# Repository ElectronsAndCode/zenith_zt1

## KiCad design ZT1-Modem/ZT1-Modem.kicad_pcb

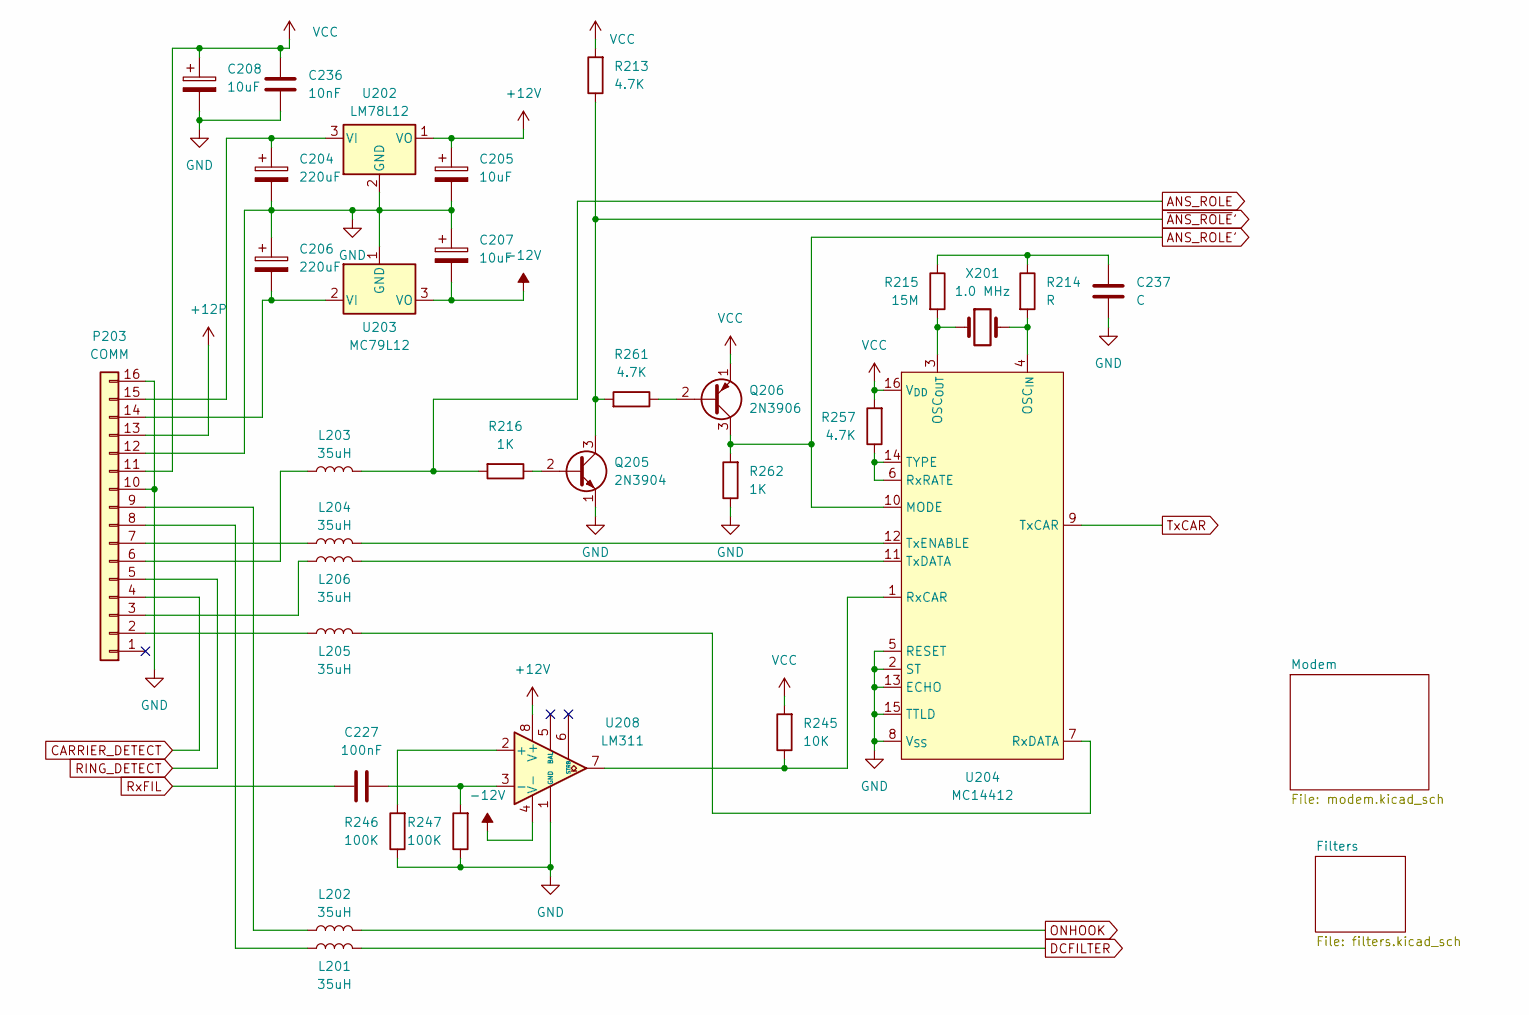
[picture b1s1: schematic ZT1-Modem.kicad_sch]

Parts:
C204, C206: 220uF; CP_Radial_Tantal_D9.0mm_P5.00mm
C205, C207, C208: 10uF; CP_Radial_Tantal_D5.0mm_P2.50mm
C227: 100nF; C_300mil
C236: 10nF; C_10mm
C237: C; C_10mm
L201, L202, L203, L204, L205, L206: 35uH; L_150mil
P203: COMM; PinHeader_1x16_P2.54mm_Vertical
Q205: 2N3904; TO-92_Inline_Wide
Q206: 2N3906; TO-92_Inline_Wide
R213, R257, R261: 4.7K; R
R214: R
R215: 15M; R
R216, R262: 1K; R
R245: 10K; R
R246, R247: 100K; R
U202: LM78L12; TO-92_Inline_Wide
U203: MC79L12; TO-92_Inline_Wide
U204: MC14412; DIP-16_W7.62mm
U208: LM311; DIP-8_W7.62mm
X201: 1.0 MHz; Crystal_HC33-U_Vertical

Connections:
+12P: P203.13; also elsewhere on the board
+12V: C205.1, U202.1 (VO), U208.8 (V+); also elsewhere on the board
-12V: C207.2, U203.3 (VO), U208.4 (V-); also elsewhere on the board
ANS_ROLE: L203.2, R216.2; also elsewhere on the board
ANS_ROLE': Q206.3 (C), R262.2, U204.10 (MODE); also elsewhere on the board
CARRIER_DETECT: P203.4; also elsewhere on the board
DCFILTER: L201.1; also elsewhere on the board
GND: C204.2, C205.2, C206.1, C207.1, C208.2, C236.1, C237.2, P203.10, P203.12, P203.16, Q205.1 (E), R246.1, R247.1, R262.1, U202.2 (GND), U203.1 (GND), U204.2 (ST), U204.5 (RESET), U204.8 (V_{SS}), U204.13 (ECHO), U204.15 (TTLD), U208.1 (GND); also elsewhere on the board
unnamed: C237.1, R214.1, R215.1
unnamed: L205.2, P203.2
unnamed: L206.1, P203.3
unnamed: L203.1, P203.6
unnamed: L204.1, P203.7
unnamed: L201.2, P203.8
unnamed: L202.2, P203.9
unnamed: C206.2, P203.14, U203.2 (VI)
unnamed: C204.1, P203.15, U202.3 (VI)
unnamed: Q205.2 (B), R216.1
unnamed: Q206.2 (B), R261.1
unnamed: R214.2, U204.4 (OSC_{IN}), X201.2
unnamed: R215.2, U204.3 (OSC_{OUT}), X201.1
unnamed: R245.1, U204.1 (RxCAR), U208.7
unnamed: L205.1, U204.7 (RxDATA)
unnamed: R257.1, U204.6 (RxRATE), U204.14 (TYPE)
unnamed: L206.2, U204.11 (TxDATA)
unnamed: L204.2, U204.12 (TxENABLE)
unnamed: R246.2, U208.2 (+)
unnamed: C227.2, R247.2, U208.3 (-)
ONHOOK: L202.1; also elsewhere on the board
RING_DETECT: P203.5; also elsewhere on the board
RxFIL: C227.1; also elsewhere on the board
TxCAR: U204.9 (TxCAR); also elsewhere on the board
VCC: C208.1, C236.2, P203.11, Q206.1 (E), R213.2, R245.2, R257.2, U204.16 (V_{DD}); also elsewhere on the board
~ANS_ROLE': Q205.3 (C), R213.1, R261.2; also elsewhere on the board

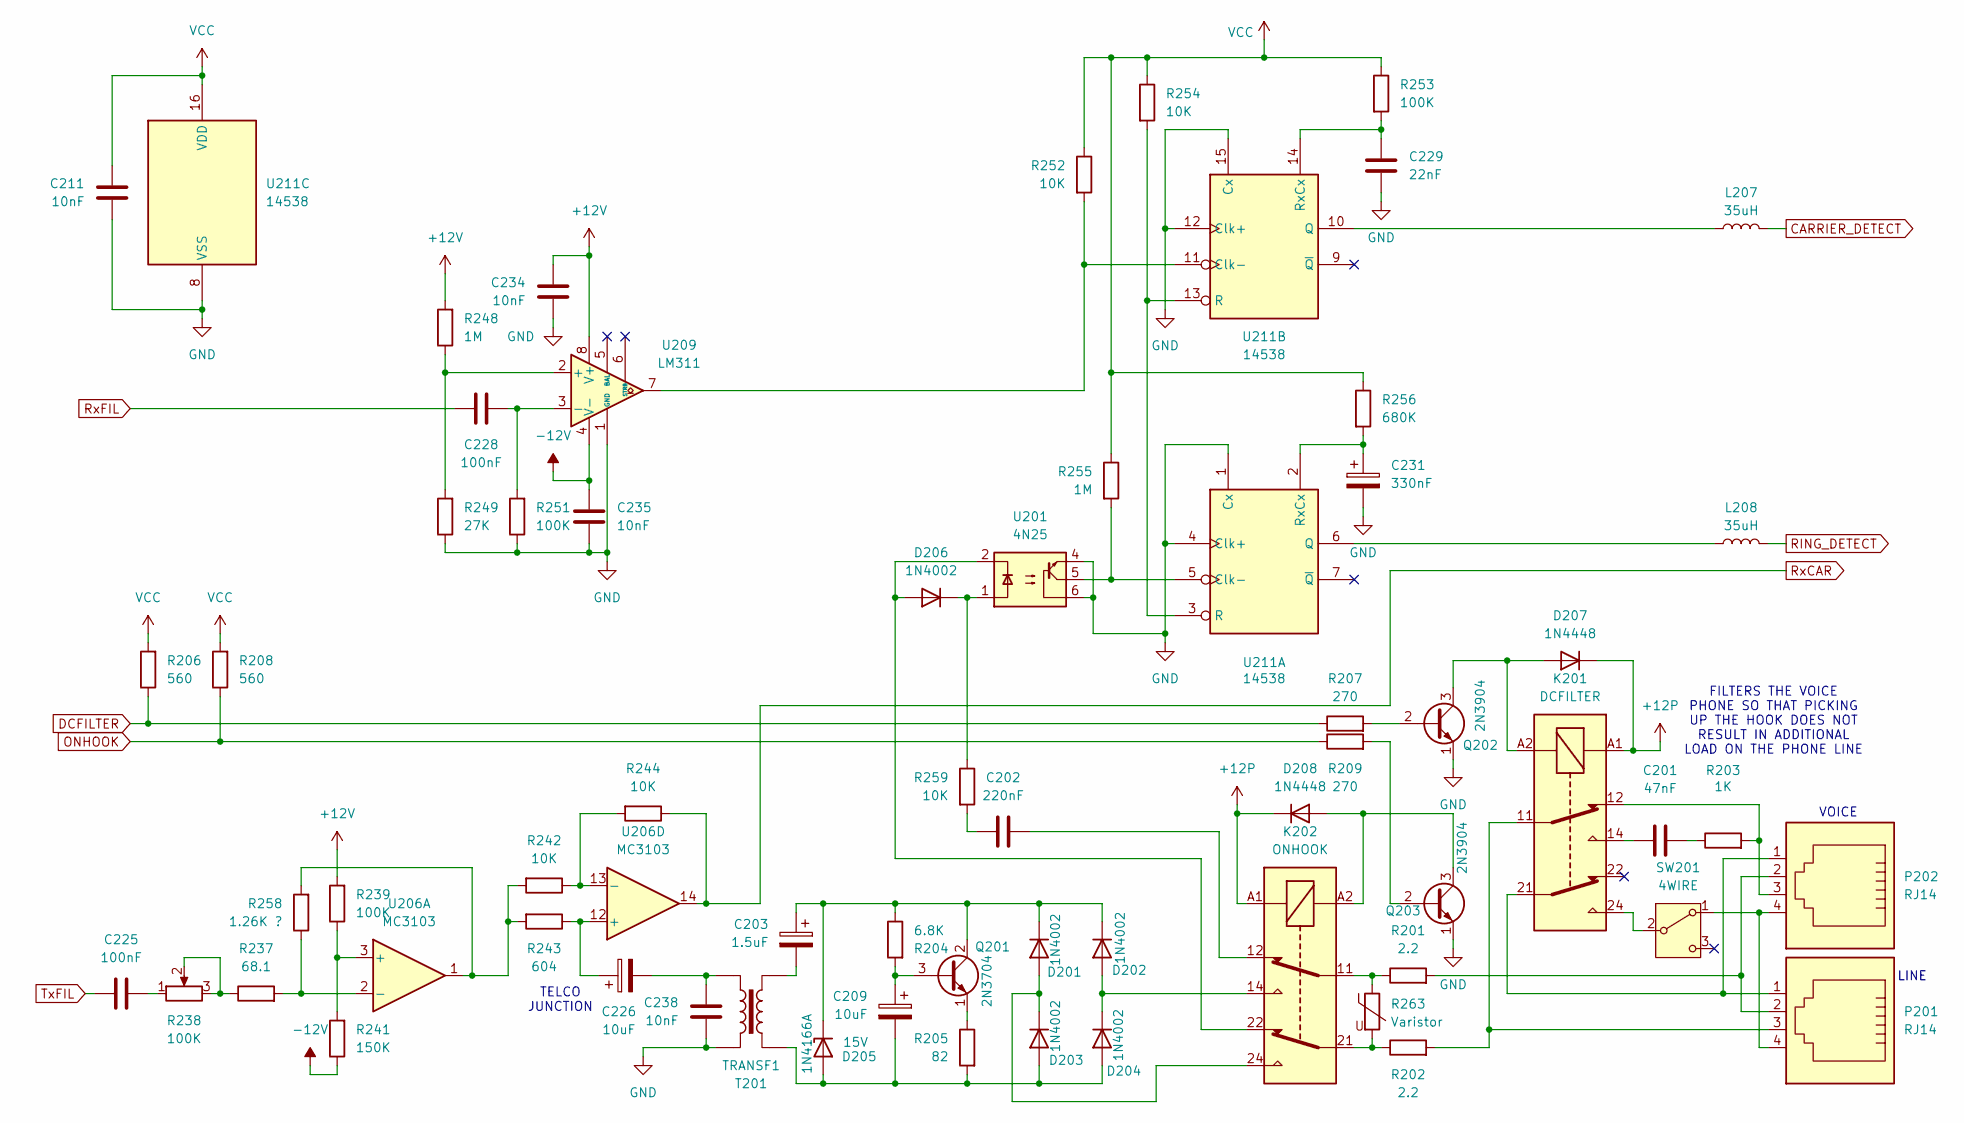
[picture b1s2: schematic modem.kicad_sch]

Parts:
C201: 47nF; C_10mm
C202: 220nF; C_Axial_L17.0mm_D6.5mm_P25.00mm_Horizontal
C203: 1.5uF; CP_Axial_L18.0mm_D8.0mm_P25.00mm_Horizontal
C209, C226: 10uF; CP_Radial_Tantal_D5.0mm_P2.50mm
C211, C234, C235, C238: 10nF; C_10mm
C225, C228: 100nF; C_300mil
C229: 22nF; L_150mil
C231: 330nF; CP_Radial_Tantal_D5.0mm_P2.50mm
D201, D202, D203, D204, D206: 1N4002; D_10mm
D205: 1N4166A; D_11.5mm
D207, D208: 1N4448; D_9mm
K201: DCFILTER; K
K202: ONHOOK; K
L207, L208: 35uH; L_150mil
P201, P202: RJ14; RJ
Q201: 2N3704; TO-92_Inline_Wide
Q202, Q203: 2N3904; TO-92_Inline_Wide
R201, R202: 2.2; R
R203: 1K; R
R204: 6.8K; R
R205: 82; R
R206, R208: 560; R
R207, R209: 270; R
R237: 68.1; R
R238: 100K; Potentiometer_Alps_RK09Y11_Single_Horizontal
R239, R251, R253: 100K; R
R241: 150K; R
R242, R244, R252, R254, R259: 10K; R
R243: 604; R
R248, R255: 1M; R
R249: 27K; R
R256: 680K; R
R258: 1.26K ?; R
R263: Varistor; RV_Disc_D12mm_W5.1mm_P7.5mm
SW201: 4WIRE; SW_PUSH_TOGGLE
T201: TRANSF1; T
U201: 4N25; DIP-6_W7.62mm
U206: MC3103; DIP-14_W7.62mm
U209: LM311; DIP-8_W7.62mm
U211: 14538; DIP-16_W7.62mm

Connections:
+12P: D207.1 (K), D208.1 (K), K201.A1, K202.A1; also elsewhere on the board
+12V: C234.1, R239.2, R248.2, U209.8 (V+); also elsewhere on the board
-12V: C235.1, R241.1, U209.4 (V-); also elsewhere on the board
CARRIER_DETECT: L207.2; also elsewhere on the board
DCFILTER: R206.1, R207.1; also elsewhere on the board
GND: C211.2, C229.2, C231.2, C234.2, C235.2, C238.2, Q202.1 (E), Q203.1 (E), R249.1, R251.1, T201.1, U201.4, U201.6, U209.1 (GND), U211.1 (Cx), U211.4 (Clk+), U211.8 (VSS), U211.12 (Clk+), U211.15 (Cx); also elsewhere on the board
unnamed: C201.1, R203.1
unnamed: C201.2, K201.14
unnamed: C202.1, R259.2
unnamed: C202.2, K202.12
unnamed: C203.2, T201.3
unnamed: C225.2, R238.1
unnamed: C226.2, C238.1, T201.2
unnamed: D201.2 (A), D203.1 (K), K202.24
unnamed: C203.1, D201.1 (K), D202.1 (K), D205.1 (K), Q201.2 (C), R204.1
unnamed: D202.2 (A), D204.1 (K), K202.14
unnamed: C209.2, D203.2 (A), D204.2 (A), D205.2 (A), R205.2, T201.4
unnamed: D206.2 (A), K202.22, U201.2
unnamed: D206.1 (K), R259.1, U201.1
unnamed: D207.2 (A), K201.A2, Q202.3 (C)
unnamed: D208.2 (A), K202.A2, Q203.3 (C)
unnamed: K201.11, P201.3, R202.2
unnamed: K201.12, P202.3, R203.2
unnamed: K201.21, P201.1, P202.1
unnamed: K202.11, R201.1, R263.1
unnamed: K202.21, R202.1, R263.2
unnamed: P201.2, P202.2, R201.2
unnamed: C209.1, Q201.3 (B), R204.2
unnamed: Q201.1 (E), R205.1
unnamed: Q202.2 (B), R207.2
unnamed: Q203.2 (B), R209.2
unnamed: R237.1, R238.2, R238.3
unnamed: R242.2, R243.2, R258.2, U206.1
unnamed: P201.4, P202.4, SW201.1 (A)
unnamed: K201.24, SW201.2 (B)
unnamed: R239.1, R241.2, U206.3 (+)
unnamed: R237.2, R258.1, U206.2 (-)
unnamed: C226.1, R243.1, U206.12 (+)
unnamed: R242.1, R244.2, U206.13 (-)
unnamed: R248.1, R249.2, U209.2 (+)
unnamed: C228.2, R251.2, U209.3 (-)
unnamed: R255.2, U201.5, U211.5 (Clk-)
unnamed: L208.1, U211.6 (Q)
unnamed: R254.2, U211.3 (R), U211.13 (R)
unnamed: C231.1, R256.2, U211.2 (RxCx)
unnamed: R252.2, U209.7, U211.11 (Clk-)
unnamed: L207.1, U211.10 (Q)
unnamed: C229.1, R253.2, U211.14 (RxCx)
ONHOOK: R208.1, R209.1; also elsewhere on the board
RING_DETECT: L208.2; also elsewhere on the board
RxCAR: R244.1, U206.14; also elsewhere on the board
RxFIL: C228.1; also elsewhere on the board
TxFIL: C225.1; also elsewhere on the board
VCC: C211.1, R206.2, R208.2, R252.1, R253.1, R254.1, R255.1, R256.1, U211.16 (VDD); also elsewhere on the board

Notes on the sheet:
VOICE
LINE
FILTERS THE VOICE PHONE SO THAT PICKING UP THE HOOK DOES NOT RESULT IN ADDITIONAL LOAD ON THE PHONE LINE
TELCO JUNCTION

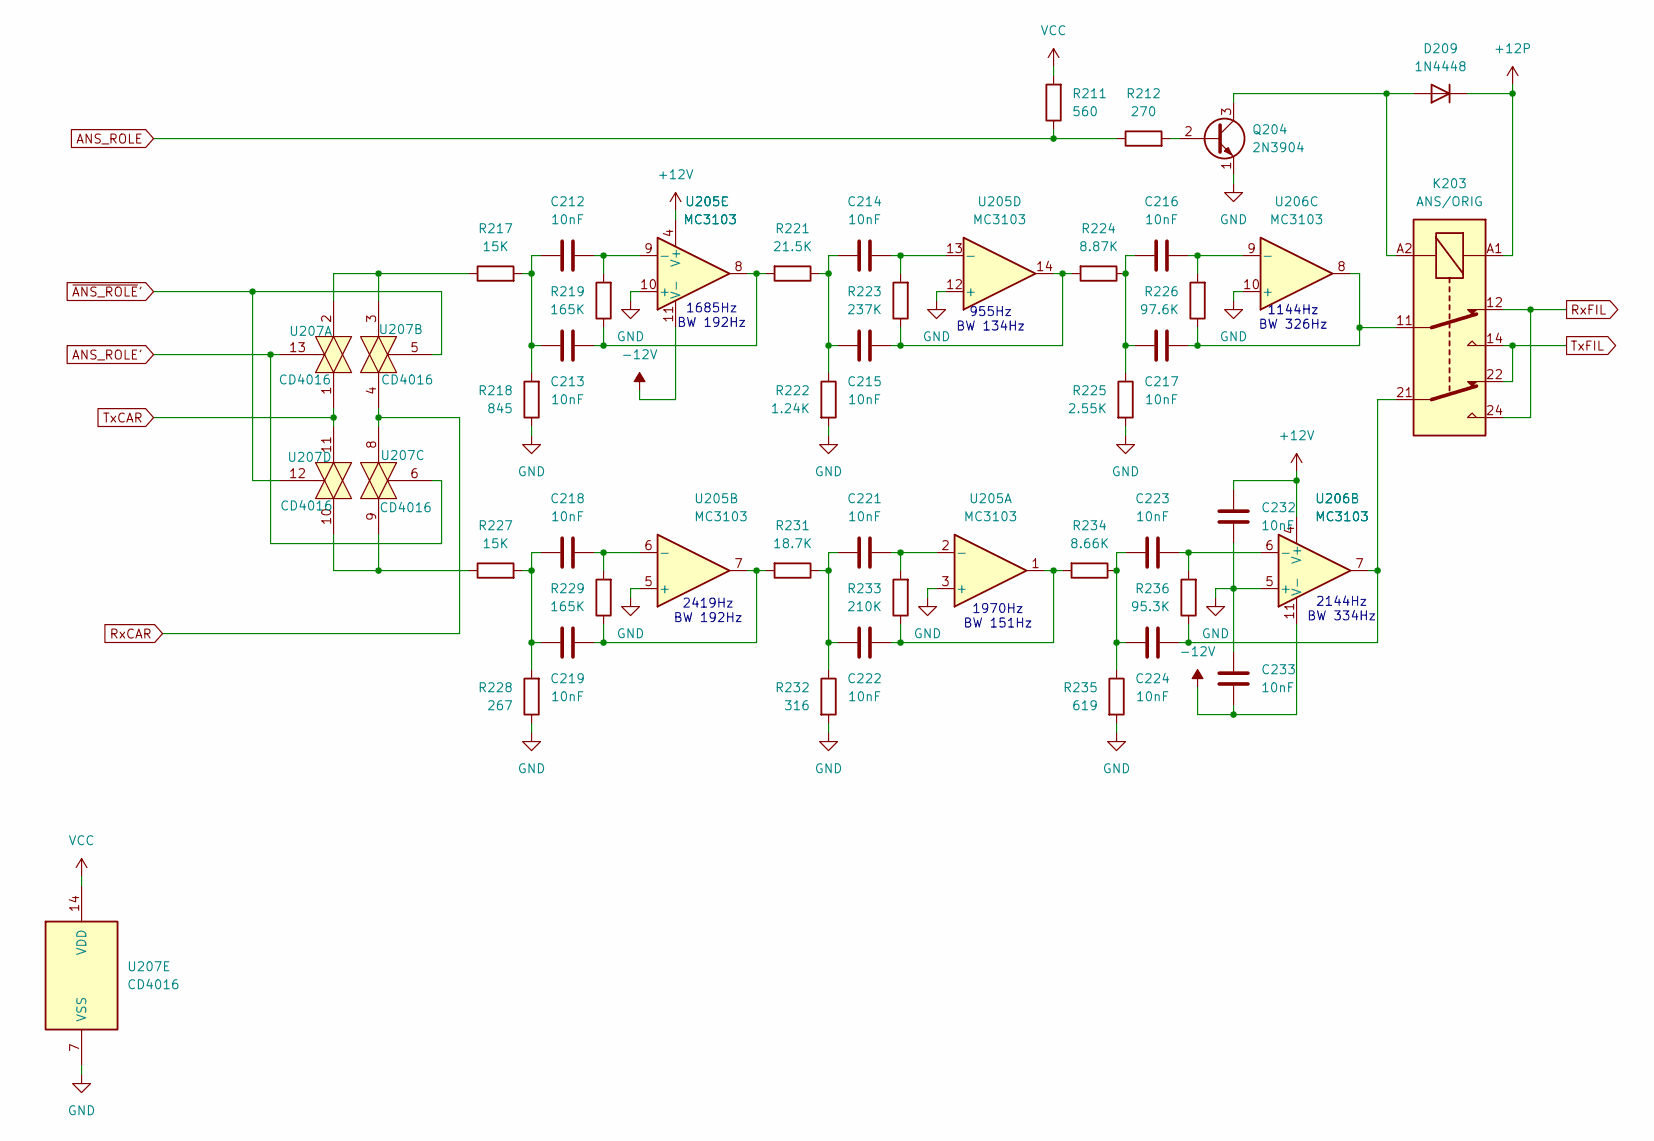
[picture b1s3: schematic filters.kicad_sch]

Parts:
C212, C213, C214, C215, C216, C217, C218, C219, C221, C222, C223, C224: 10nF; C_16mm
C232, C233: 10nF; C_10mm
D209: 1N4448; D_9mm
K203: ANS/ORIG; K
Q204: 2N3904; TO-92_Inline_Wide
R211: 560; R
R212: 270; R
R217, R227: 15K; R
R218: 845; R
R219, R229: 165K; R
R221: 21.5K; R
R222: 1.24K; R
R223: 237K; R
R224: 8.87K; R
R225: 2.55K; R
R226: 97.6K; R
R228: 267; R
R231: 18.7K; R
R232: 316; R
R233: 210K; R
R234: 8.66K; R
R235: 619; R
R236: 95.3K; R
U205, U206: MC3103; DIP-14_W7.62mm
U207: CD4016; DIP-14_W7.62mm

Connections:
+12P: D209.1 (K), K203.A1; also elsewhere on the board
+12V: C232.2, U205.4 (V+), U206.4 (V+); also elsewhere on the board
-12V: C233.1, U205.11 (V-), U206.11 (V-); also elsewhere on the board
ANS_ROLE: R211.1, R212.1; also elsewhere on the board
ANS_ROLE': U207.6, U207.13; also elsewhere on the board
GND: C232.1, C233.2, Q204.1 (E), R218.1, R222.2, R225.2, R228.1, R232.2, R235.2, U205.3 (+), U205.5 (+), U205.10 (+), U205.12 (+), U206.5 (+), U206.10 (+), U207.7 (VSS); also elsewhere on the board
unnamed: C212.1, C213.1, R217.2, R218.2
unnamed: C213.2, R219.1, R221.2, U205.8
unnamed: C214.1, C215.1, R221.1, R222.1
unnamed: C215.2, R223.1, R224.2, U205.14
unnamed: C216.1, C217.1, R224.1, R225.1
unnamed: C217.2, K203.11, R226.1, U206.8
unnamed: C218.1, C219.1, R227.2, R228.2
unnamed: C219.2, R229.1, R231.2, U205.7
unnamed: C221.1, C222.1, R231.1, R232.1
unnamed: C222.2, R233.1, R234.2, U205.1
unnamed: C223.1, C224.1, R234.1, R235.1
unnamed: C224.2, K203.21, R236.1, U206.7
unnamed: D209.2 (A), K203.A2, Q204.3 (C)
unnamed: Q204.2 (B), R212.2
unnamed: R217.1, U207.2, U207.3
unnamed: R227.1, U207.9, U207.10
unnamed: C221.2, R233.2, U205.2 (-)
unnamed: C218.2, R229.2, U205.6 (-)
unnamed: C212.2, R219.2, U205.9 (-)
unnamed: C214.2, R223.2, U205.13 (-)
unnamed: C223.2, R236.2, U206.6 (-)
unnamed: C216.2, R226.2, U206.9 (-)
RxCAR: U207.4, U207.8; also elsewhere on the board
RxFIL: K203.12, K203.24; also elsewhere on the board
TxCAR: U207.1, U207.11; also elsewhere on the board
TxFIL: K203.14, K203.22; also elsewhere on the board
VCC: R211.2, U207.14 (VDD); also elsewhere on the board
~ANS_ROLE': U207.5, U207.12; also elsewhere on the board

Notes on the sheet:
2144Hz BW 334Hz
955Hz BW 134Hz
1970Hz BW 151Hz
1144Hz BW 326Hz
1685Hz BW 192Hz
2419Hz BW 192Hz

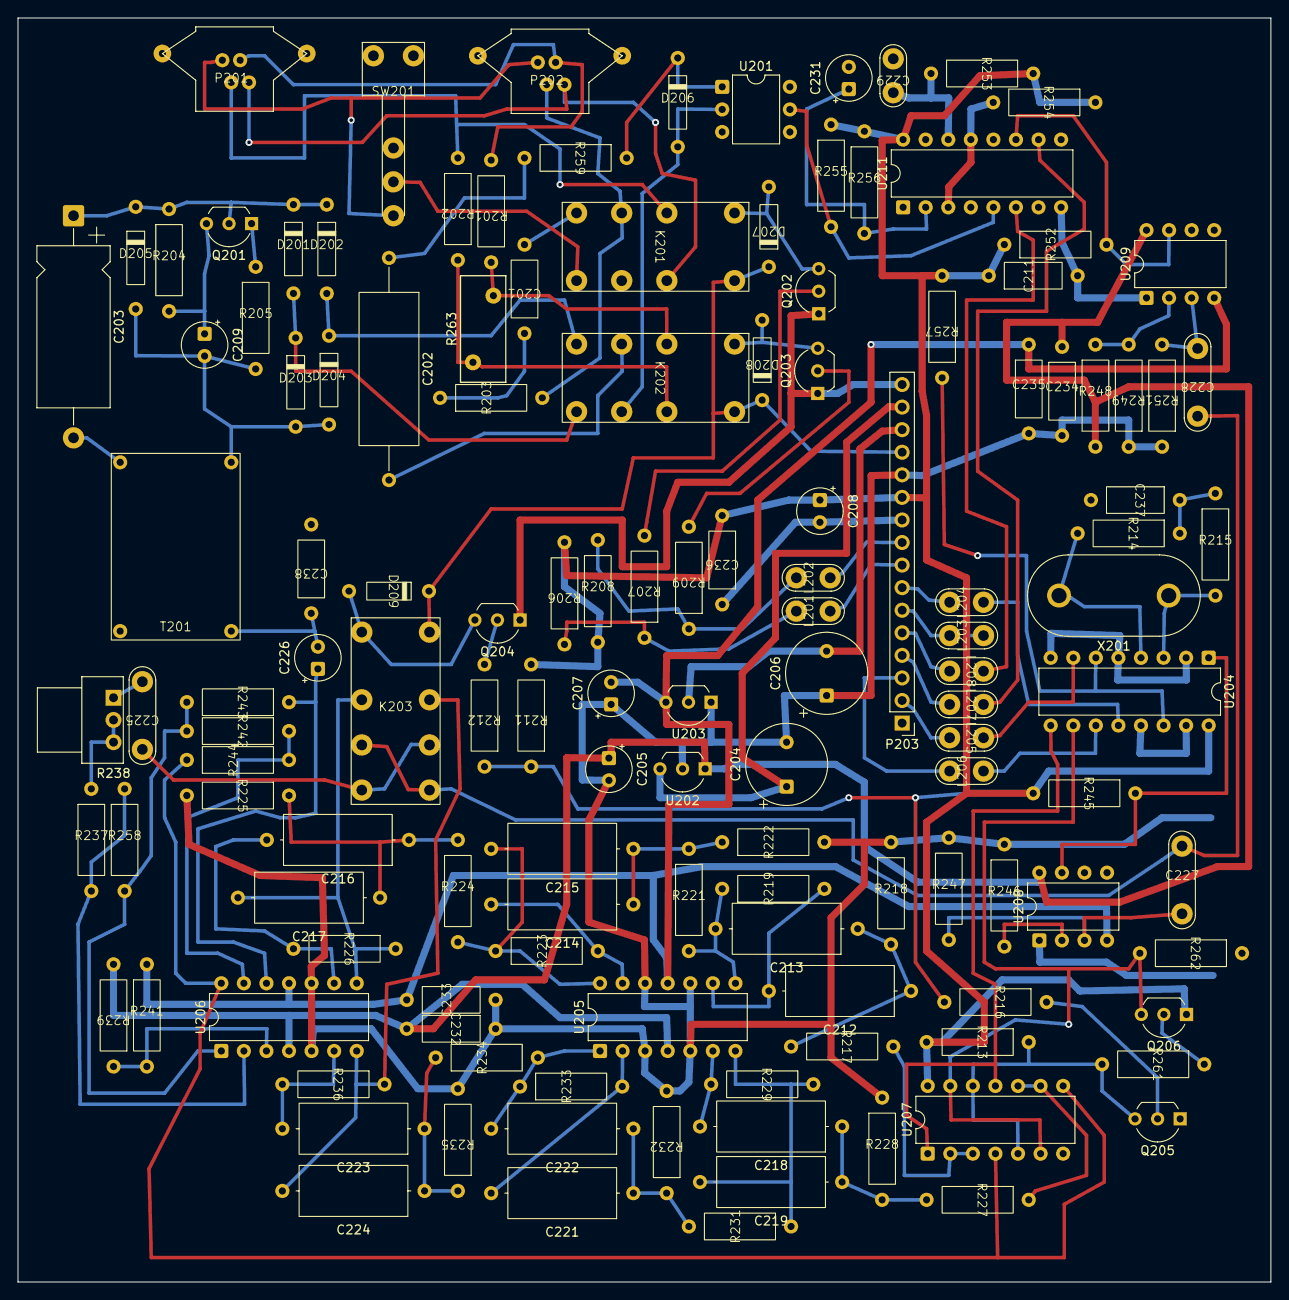
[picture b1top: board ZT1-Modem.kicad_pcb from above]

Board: 2 copper layers, 141.0 x 142.2 mm, 134 parts (0 on the bottom side), 100 nets.

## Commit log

2025-11-17 Minor touchups
    Fixed some of the text
    Added some explanations
    Simplified the video circuit
2025-11-17 Added modem schematic
2025-11-17 Generated new schematics for ZT1 mainboard
